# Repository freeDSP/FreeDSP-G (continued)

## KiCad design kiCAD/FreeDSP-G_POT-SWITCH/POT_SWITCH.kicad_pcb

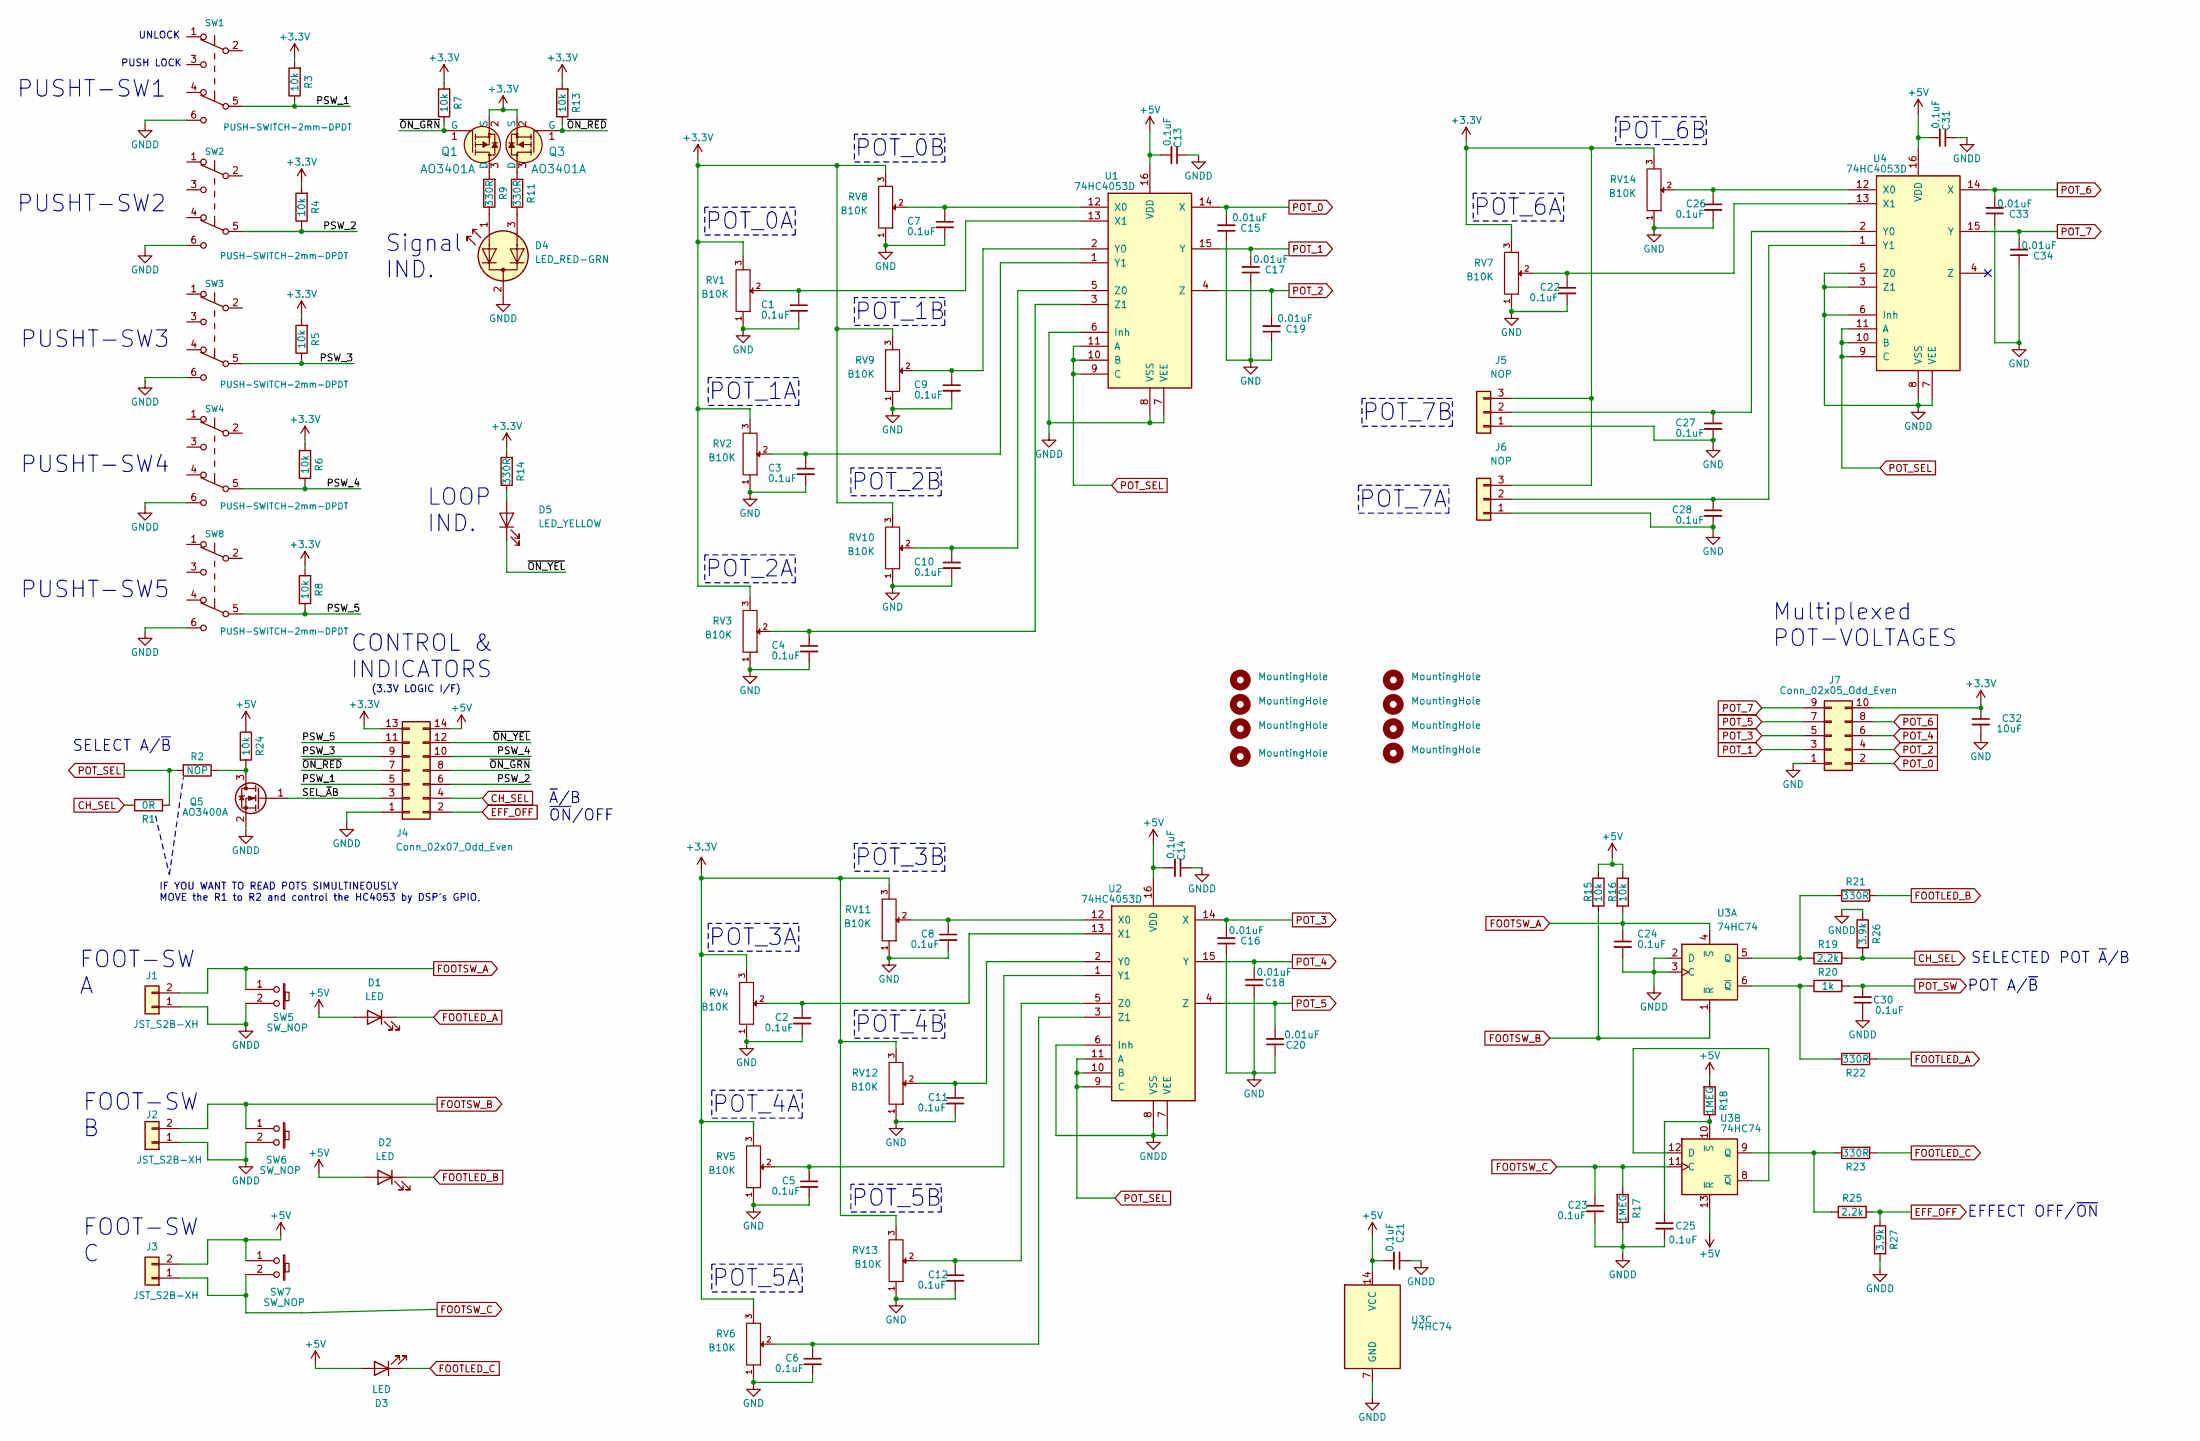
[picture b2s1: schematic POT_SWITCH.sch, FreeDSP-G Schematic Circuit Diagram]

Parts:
C1, C2, C3, C4, C5, C6, C7, C8, C9, C10, C11, C12, C13, C14, C21, C22, C23, C24, C25, C26, C27, C28, C30, C31: 0.1uF; C_0805_2012Metric_Pad1.18x1.45mm_HandSolder
C15, C16, C17, C18, C19, C20, C33, C34: 0.01uF; C_0805_2012Metric_Pad1.18x1.45mm_HandSolder
C32: 10uF; C_0805_2012Metric_Pad1.18x1.45mm_HandSolder
D1, D2, D3: LED; LED_D3.0mm_Clear
D4: LED_RED-GRN; LED_D3.0mm-3
D5: LED_YELLOW; LED_D3.0mm
H1, H2, H3, H4, H5, H6, H7, H8: MountingHole; MountingHole_3.2mm_M3_DIN965_Pad_TopBottom
J1, J2, J3: JST_S2B-XH; JST_XH_S2B-XH-A_1x02_P2.50mm_Horizontal
J4: Conn_02x07_Odd_Even; IDC-Header_2x07_P2.54mm_Horizontal
J5, J6: NOP; JST_XH_B3B-XH-A_1x03_P2.50mm_Vertical
J7: Conn_02x05_Odd_Even; IDC-Header_2x05_P2.54mm_Horizontal
Q1, Q3: AO3401A; SOT-23-3; MPN AO3401A; Digi-Key_PN 785-1001-1-ND
Q5: AO3400A; SOT-23
R1: 0R; R_0805_2012Metric_Pad1.20x1.40mm_HandSolder
R2: NOP; R_0805_2012Metric_Pad1.20x1.40mm_HandSolder
R3, R4, R5, R6, R7, R8, R13, R15, R16, R24: 10k; R_0805_2012Metric_Pad1.20x1.40mm_HandSolder
R9, R11, R14, R21, R22, R23: 330R; R_0805_2012Metric_Pad1.20x1.40mm_HandSolder
R17, R18: 1MEG; R_0805_2012Metric_Pad1.20x1.40mm_HandSolder
R19, R25: 2.2k; R_0805_2012Metric_Pad1.20x1.40mm_HandSolder
R20: 1k; R_0805_2012Metric_Pad1.20x1.40mm_HandSolder
R26, R27: 3.9k; R_0805_2012Metric_Pad1.20x1.40mm_HandSolder
RV1, RV2, RV3, RV4, RV5, RV6, RV7, RV8, RV9, RV10, RV11, RV12, RV13, RV14: B10K; Alps_RK09K113
SW1, SW2, SW3, SW4, SW8: PUSH-SWITCH-2mm-DPDT; PUSHSW_DPDT_6-7mm
SW5, SW6, SW7: SW_NOP; MJTP1250
U1, U2, U4: 74HC4053D; DIP-16_W7.62mm
U3: 74HC74; DIP-14_W7.62mm

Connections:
+3V3: C32.1, J4.13, J5.3, J6.3, J7.10, Q1.2 (S), Q3.2 (S), R3.2, R4.2, R5.2, R6.2, R7.2, R8.2, R13.2, R14.2, RV1.3, RV2.3, RV3.3, RV4.3, RV5.3, RV6.3, RV7.3, RV8.3, RV9.3, RV10.3, RV11.3, RV12.3, RV13.3, RV14.3
+5V: C13.2, C14.2, C21.2, C31.2, D1.2 (A), D2.2 (A), D3.2 (A), J3.2, J4.14, R15.1, R16.1, R18.2, R24.1, SW7.1, U1.16 (VDD), U2.16 (VDD), U3.13 (~R), U3.14 (VCC), U4.16 (VDD)
/PSW_1: J4.5, R3.1, SW1.5 (B)
/PSW_2: J4.6, R4.1, SW2.5 (B)
/PSW_3: J4.9, R5.1, SW3.5 (B)
/PSW_4: J4.10, R6.1, SW4.5 (B)
/PSW_5: J4.11, R8.1, SW8.5 (B)
/SEL_~A~B: J4.3, Q5.1 (G)
/~ON_GRN: J4.8, Q1.1 (G), R7.1
/~ON_OVF: D5.1 (K), J4.12
/~ON_RED: J4.7, Q3.1 (G), R13.1
CH_SEL: J4.4, R1.1, R19.2, R26.2
EFF_OFF: J4.2, R25.2, R27.1
FOOTLED_A: D1.1 (K), R22.2
FOOTLED_B: D2.1 (K), R21.2
FOOTLED_C: D3.1 (K), R23.2
FOOTSW_A: C24.1, J1.2, R16.2, SW5.1, U3.4 (~S)
FOOTSW_B: J2.2, R15.2, SW6.1, U3.1 (~R)
FOOTSW_C: C23.1, J3.1, R17.2, SW7.2, U3.11 (C)
GND: C1.2, C2.2, C3.2, C4.2, C5.2, C6.2, C7.2, C8.2, C9.2, C10.2, C11.2, C12.2, C15.1, C16.1, C17.1, C18.1, C19.1, C20.1, C22.2, C26.2, C27.2, C28.2, C32.2, C33.1, C34.1, J5.1, J6.1, J7.1, RV1.1, RV2.1, RV3.1, RV4.1, RV5.1, RV6.1, RV7.1, RV8.1, RV9.1, RV10.1, RV11.1, RV12.1, RV13.1, RV14.1
GNDD: C13.1, C14.1, C21.1, C23.2, C24.2, C25.2, C30.1, C31.1, D4.2 (K), J1.1, J2.1, J4.1, Q5.2 (S), R17.1, R26.1, R27.2, SW1.6 (C), SW2.6 (C), SW3.6 (C), SW4.6 (C), SW5.2, SW6.2, SW8.6 (C), U1.6 (Inh), U1.7 (VEE), U1.8 (VSS), U2.6 (Inh), U2.7 (VEE), U2.8 (VSS), U3.2 (D), U3.3 (C), U3.7 (GND), U4.3 (Z1), U4.5 (Z0), U4.6 (Inh), U4.7 (VEE), U4.8 (VSS)
unnamed: C1.1, RV1.2, U1.13 (X1)
unnamed: C2.1, RV4.2, U2.13 (X1)
unnamed: C3.1, RV2.2, U1.1 (Y1)
unnamed: C4.1, RV3.2, U1.3 (Z1)
unnamed: C5.1, RV5.2, U2.1 (Y1)
unnamed: C6.1, RV6.2, U2.3 (Z1)
unnamed: C7.1, RV8.2, U1.12 (X0)
unnamed: C8.1, RV11.2, U2.12 (X0)
unnamed: C9.1, RV9.2, U1.2 (Y0)
unnamed: C10.1, RV10.2, U1.5 (Z0)
unnamed: C11.1, RV12.2, U2.2 (Y0)
unnamed: C12.1, RV13.2, U2.5 (Z0)
unnamed: C22.1, RV7.2, U4.13 (X1)
unnamed: C25.1, R18.1, U3.10 (~S)
unnamed: C26.1, RV14.2, U4.12 (X0)
unnamed: C27.1, J5.2, U4.2 (Y0)
unnamed: C28.1, J6.2, U4.1 (Y1)
unnamed: D4.1 (A1), R9.1
unnamed: D4.3 (A2), R11.1
unnamed: D5.2 (A), R14.1
unnamed: Q1.3 (D), R9.2
unnamed: Q3.3 (D), R11.2
unnamed: Q5.3 (D), R2.1, R24.2
unnamed: R19.1, R21.1, U3.5 (Q)
unnamed: R20.1, R22.1, U3.6 (~Q)
unnamed: R23.1, R25.1, U3.9 (Q)
unnamed: U3.8 (~Q), U3.12 (D)
POT_0: C15.2, J7.2, U1.14 (X)
POT_1: C17.2, J7.3, U1.15 (Y)
POT_2: C19.2, J7.4, U1.4 (Z)
POT_3: C16.2, J7.5, U2.14 (X)
POT_4: C18.2, J7.6, U2.15 (Y)
POT_5: C20.2, J7.7, U2.4 (Z)
POT_6: C33.2, J7.8, U4.14 (X)
POT_7: C34.2, J7.9, U4.15 (Y)
POT_SEL: R1.2, R2.2, U1.9 (C), U1.10 (B), U1.11 (A), U2.9 (C), U2.10 (B), U2.11 (A), U4.9 (C), U4.10 (B), U4.11 (A)
POT_SW: C30.2, R20.2

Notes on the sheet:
POT_0A
POT_0B
POT_1B
POT_2B
POT_1A
POT_2A
POT_3B
POT_4B
POT_5B
POT_3A
POT_4A
POT_5A
POT_6A
POT_6B
FOOT-SW C
FOOT-SW B
FOOT-SW A
PUSHT-SW1
Multiplexed POT-VOLTAGES
PUSHT-SW4
PUSHT-SW3
POT_7A
POT_7B
CONTROL & INDICATORS
PUSHT-SW2
UNLOCK
PUSH LOCK
POT A/~B
SELECTED POT ~A~/B
SELECT A/~B
EFFECT OFF/~ON
(3.3V LOGIC I/F)
~A~/B
~ON~/OFF
IF YOU WANT TO READ POTS SIMULTINEOUSLY MOVE the R1 to R2 and control the HC4053 by DSP’s GPIO,
PUSHT-SW5
Signal IND.
LOOP IND.

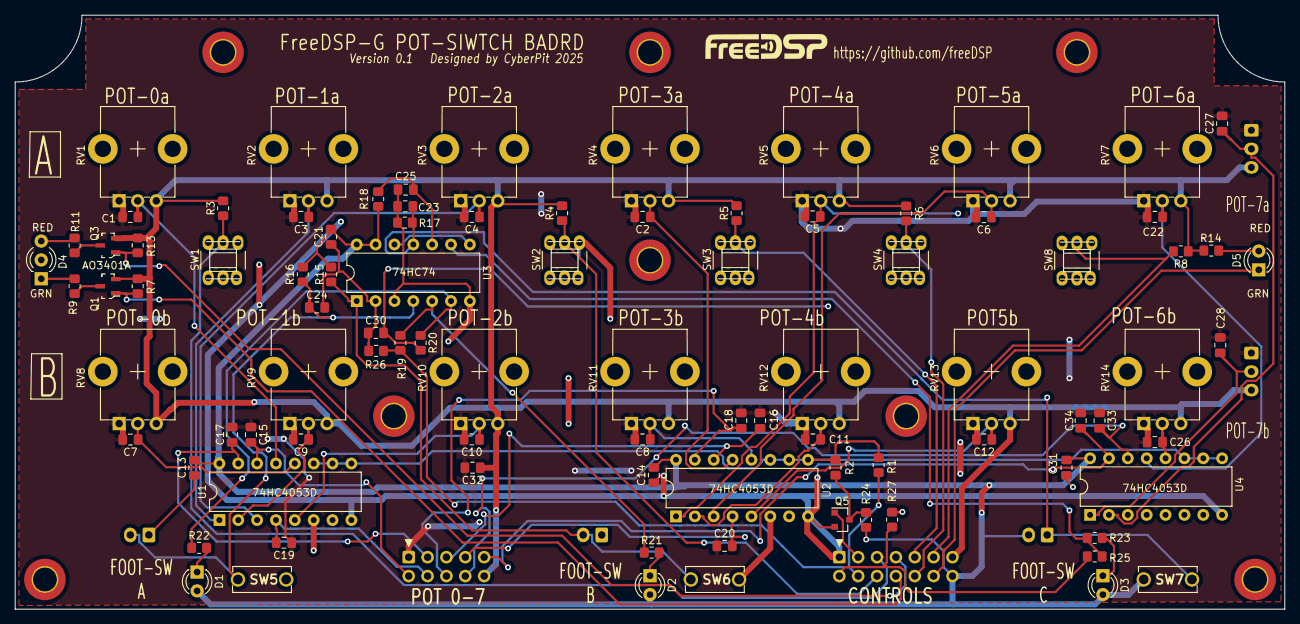
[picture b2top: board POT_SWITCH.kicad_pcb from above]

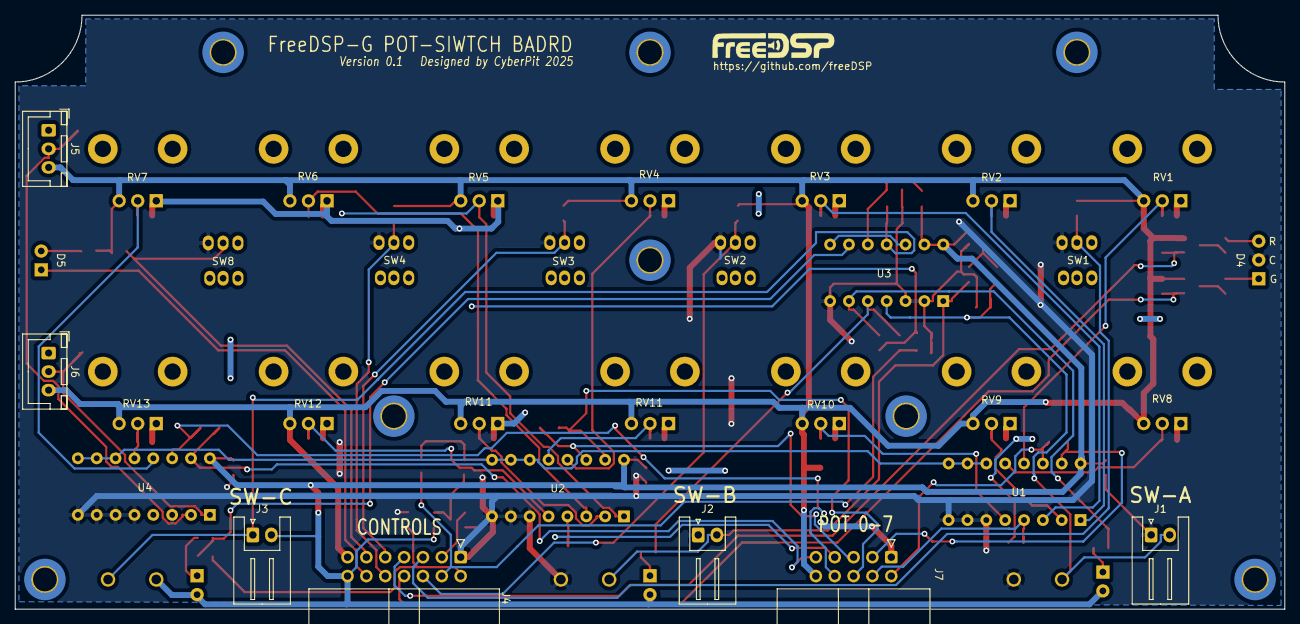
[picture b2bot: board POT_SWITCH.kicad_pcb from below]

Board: 2 copper layers, 171.0 x 80.0 mm, 107 parts (7 on the bottom side), 58 nets.

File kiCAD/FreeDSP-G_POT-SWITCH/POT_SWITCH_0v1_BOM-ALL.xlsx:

Designator | Quantity | Package | Designation | JLCPCB#
C32 | 1 | C_0805_2012Metric_Pad1.18x1.45mm_HandSolder | 10uF | C15850
C34,C33,C20,C19,C18,C17,C16,C15 | 8 | C_0805_2012Metric_Pad1.18x1.45mm_HandSolder | 0.01uF | C1710
C6,C31,C30,C28,C27,C26,C25,C24,C23,C22,C21,C14,C13,C12,C11,C10,C9,C8,C7,C5,C4,C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 | 24 | C_0805_2012Metric_Pad1.18x1.45mm_HandSolder | 0.1uF | C49678
Q3,Q1 | 2 | SOT-23-3 | AO3401A | C15127
Q5 | 1 | SOT-23 | AO3400A | C20917
R1 | 1 | R_0805_2012Metric_Pad1.20x1.40mm_HandSolder | 0R | C17477
R18,R17 | 2 | R_0805_2012Metric_Pad1.20x1.40mm_HandSolder | 1MEG | C17514
R20 | 1 | R_0805_2012Metric_Pad1.20x1.40mm_HandSolder | 1k | C17513
R23,R22,R21,R14,R11,R9 | 6 | R_0805_2012Metric_Pad1.20x1.40mm_HandSolder | 330R | C17630
R25,R19 | 2 | R_0805_2012Metric_Pad1.20x1.40mm_HandSolder | 2.2k | C17520
R27,R26 | 2 | R_0805_2012Metric_Pad1.20x1.40mm_HandSolder | 3.3k | C26010
R8,R24,R16,R15,R13,R7,R6,R5,R4,R3 | 10 | R_0805_2012Metric_Pad1.20x1.40mm_HandSolder | 10k | C17414

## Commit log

2025-03-21 Initial Release
2025-05-14 Modified Parameters, AUX mute fixed, BM83 enabled
2025-05-21 BM83 Power Rail Connected. Initial Reset Changd.
2025-05-21 BM83 Power Connected. Reset circuit changed.
2025-06-02 Fixed BT/DSP-Reset/Decouple-C
2025-06-02 Fixed BT/DSP-Reset/Decouple-Cap
